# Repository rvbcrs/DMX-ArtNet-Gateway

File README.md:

# DMX-ArtNet-Gateway
ESP32 ArtNet Wifi Gateway

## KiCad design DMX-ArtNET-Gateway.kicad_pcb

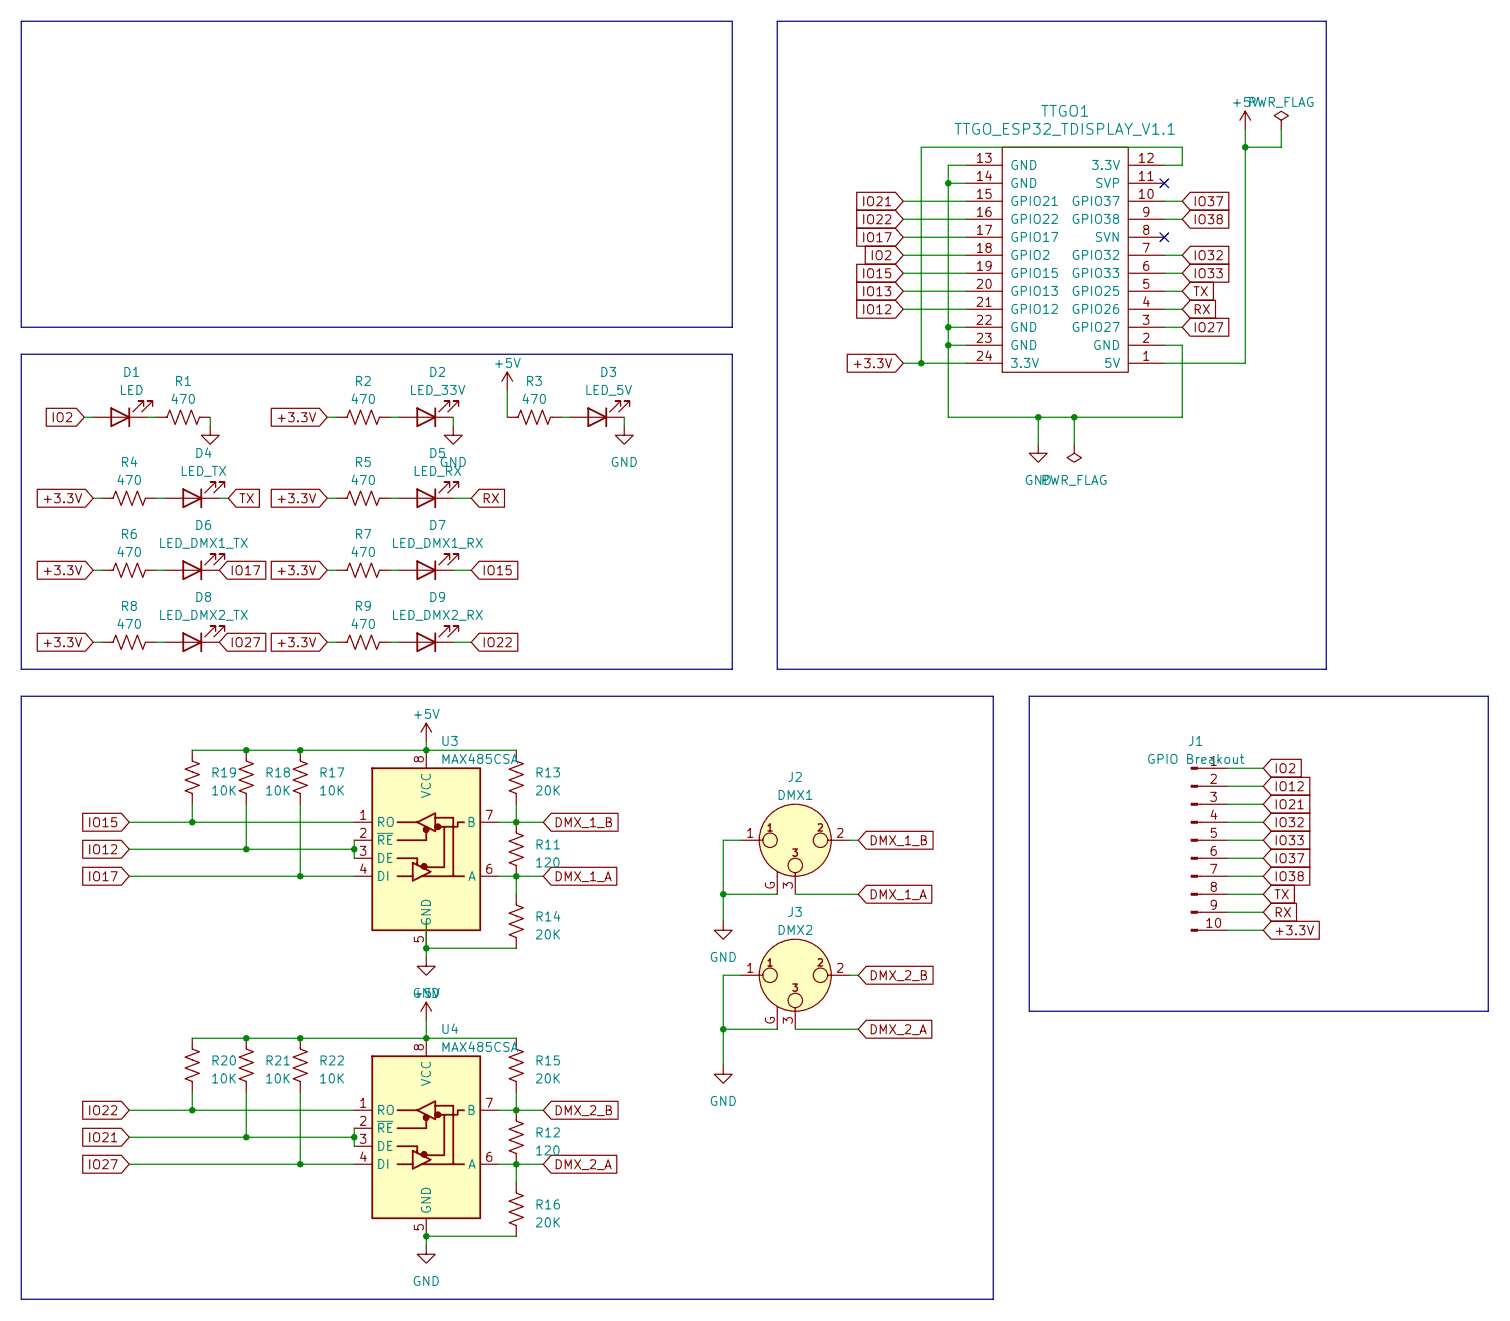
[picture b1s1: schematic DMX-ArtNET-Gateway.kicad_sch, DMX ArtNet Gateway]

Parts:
D1: LED; LED_0805_2012Metric
D2: LED_33V; LED_0805_2012Metric
D3: LED_5V; LED_0805_2012Metric
D4: LED_TX; LED_0805_2012Metric
D5: LED_RX; LED_0805_2012Metric
D6: LED_DMX1_TX; LED_0805_2012Metric
D7: LED_DMX1_RX; LED_0805_2012Metric
D8: LED_DMX2_TX; LED_0805_2012Metric
D9: LED_DMX2_RX; LED_0805_2012Metric
J1: GPIO Breakout; PinHeader_1x10_P2.54mm_Vertical
J2: DMX1; Jack_XLR_Neutrik_NC3FAH2-0_Horizontal
J3: DMX2; Jack_XLR_Neutrik_NC3FAH2-0_Horizontal
R1, R2, R3, R4, R5, R6, R7, R8, R9: 470; R_0805_2012Metric
R11, R12: 120; R_0805_2012Metric
R13, R14, R15, R16: 20K; R_0805_2012Metric
R17, R18, R19, R20, R21, R22: 10K; R_0805_2012Metric
TTGO1: TTGO_ESP32_TDISPLAY_V1.1; TTGO_ESP32_TDisplay_v1.1
U3, U4: MAX485CSA; SOIC127P600X175-8N

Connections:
+3.3V: J1.10, R2.1, R4.1, R5.1, R6.1, R7.1, R8.1, R9.1, TTGO1.12 (3.3V), TTGO1.24 (3.3V)
+5V: R3.1, R13.1, R15.1, R17.1, R18.1, R19.1, R20.1, R21.1, R22.1, TTGO1.1 (5V), U3.8 (VCC), U4.8 (VCC)
DMX_1_A: J2.3, R11.2, R14.1, U3.6 (A)
DMX_1_B: J2.2, R11.1, R13.2, U3.7 (B)
DMX_2_A: J3.3, R12.2, R16.1, U4.6 (A)
DMX_2_B: J3.2, R12.1, R15.2, U4.7 (B)
GND: D2.1 (K), D3.1 (K), J2.1, J2.G, J3.1, J3.G, R1.2, R14.2, R16.2, TTGO1.2 (GND), TTGO1.13 (GND), TTGO1.14 (GND), TTGO1.22 (GND), TTGO1.23 (GND), U3.5 (GND), U4.5 (GND)
IO2: D1.2 (A), J1.1, TTGO1.18 (GPIO2)
IO12: J1.2, R18.2, TTGO1.21 (GPIO12), U3.2 (~RE), U3.3 (DE)
IO13: TTGO1.20 (GPIO13)
IO15: D7.1 (K), R19.2, TTGO1.19 (GPIO15), U3.1 (RO)
IO17: D6.1 (K), R17.2, TTGO1.17 (GPIO17), U3.4 (DI)
IO21: J1.3, R21.2, TTGO1.15 (GPIO21), U4.2 (~RE), U4.3 (DE)
IO22: D9.1 (K), R20.2, TTGO1.16 (GPIO22), U4.1 (RO)
IO27: D8.1 (K), R22.2, TTGO1.3 (GPIO27), U4.4 (DI)
IO32: J1.4, TTGO1.7 (GPIO32)
IO33: J1.5, TTGO1.6 (GPIO33)
IO37: J1.6, TTGO1.10 (GPIO37)
IO38: J1.7, TTGO1.9 (GPIO38)
unnamed: D1.1 (K), R1.1
unnamed: D2.2 (A), R2.2
unnamed: D3.2 (A), R3.2
unnamed: D4.2 (A), R4.2
unnamed: D5.2 (A), R5.2
unnamed: D6.2 (A), R6.2
unnamed: D7.2 (A), R7.2
unnamed: D8.2 (A), R8.2
unnamed: D9.2 (A), R9.2
RX: D5.1 (K), J1.9, TTGO1.4 (GPIO26)
TX: D4.1 (K), J1.8, TTGO1.5 (GPIO25)

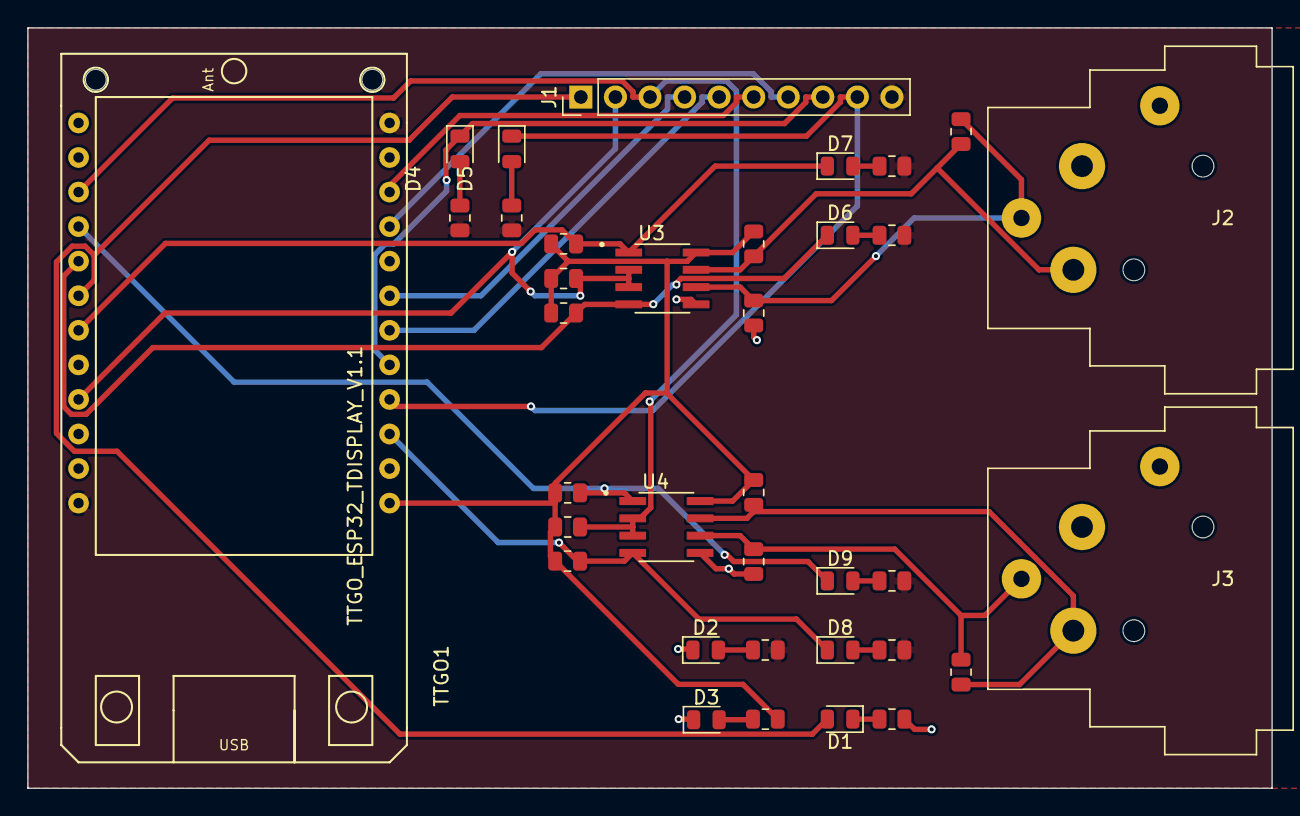
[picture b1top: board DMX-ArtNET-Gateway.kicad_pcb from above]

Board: 2 copper layers, 91.4 x 55.9 mm, 36 parts (0 on the bottom side), 29 nets.

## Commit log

2023-09-07 Firmware checkin
2023-09-08 Usbc WIP
2023-09-08 Reparatie foute checkin
2023-09-08 Versie met TTGO-Display
